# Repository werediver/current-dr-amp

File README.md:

# CURRENT DR.

This is a "current drive" or VCCS class A headphone amplifier. Some advocacy of current drive (as well as a whole book on the topic) can be found at [current-drive.info](https://www.current-drive.info/6).

The first prototype is briefly described on [Prototype](texts/prototype.md) page.

## Schematic

The current version of the schematic is showed below.

Two such channels with a dedicated [linear PSU](texts/psu.md) are going to be fit into an extruded aluminum enclosure with internal dimensions of 96x155x50 mm.

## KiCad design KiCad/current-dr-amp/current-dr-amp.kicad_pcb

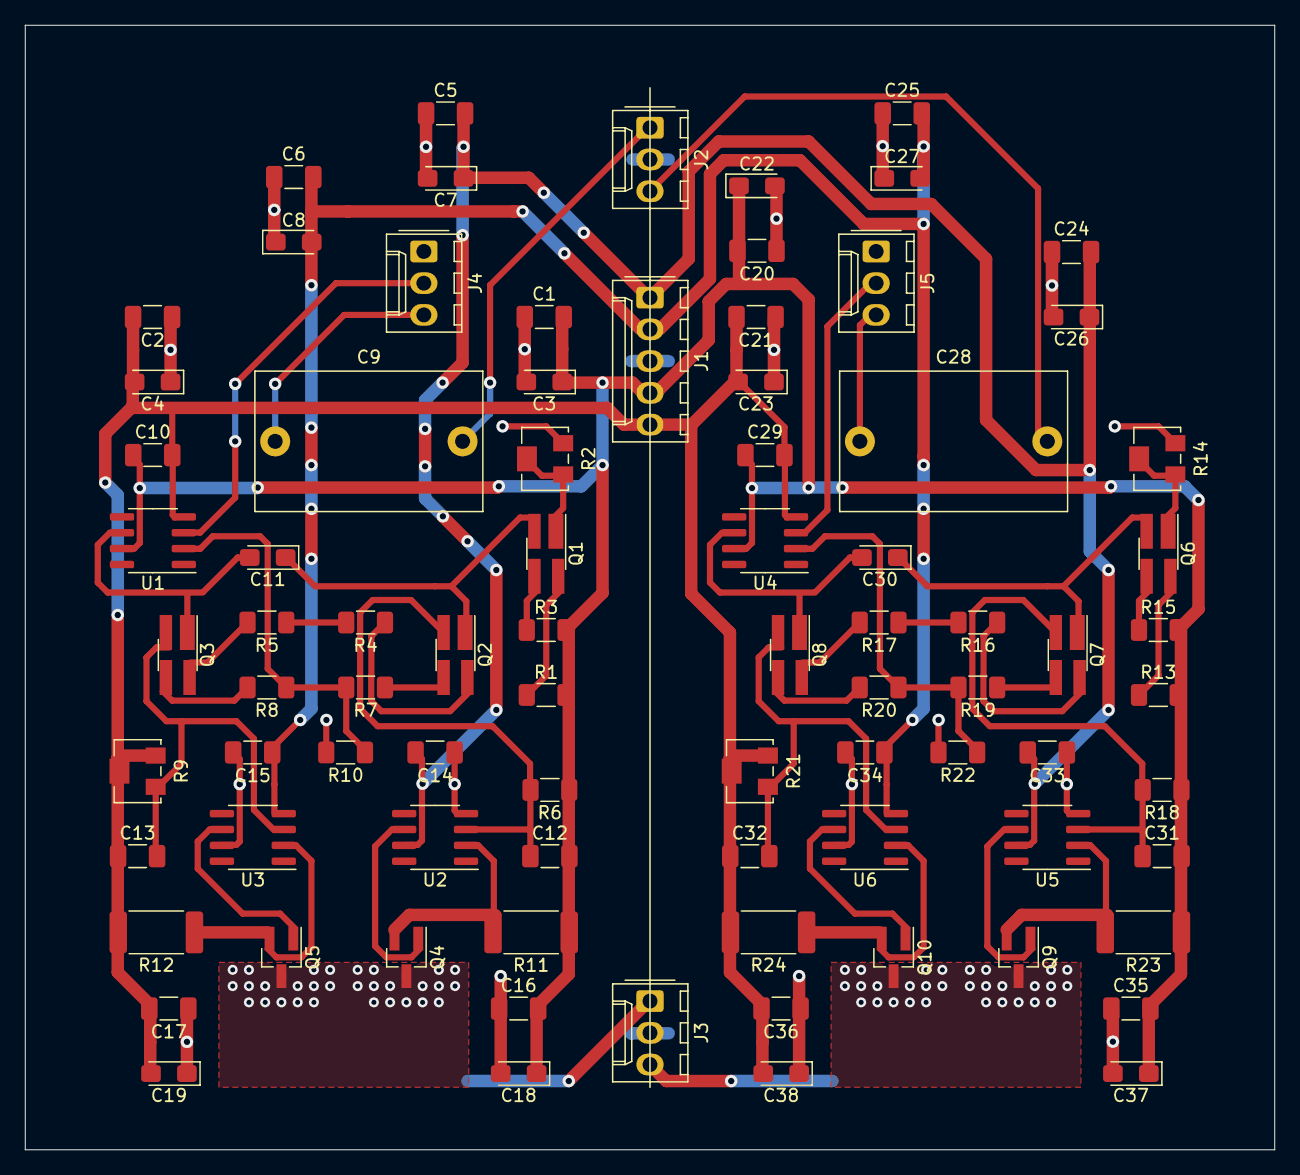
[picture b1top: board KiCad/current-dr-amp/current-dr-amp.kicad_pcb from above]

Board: 2 copper layers, 100.0 x 90.0 mm, 83 parts (0 on the bottom side), 47 nets.

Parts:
C1, C2, C5, C6, C10, C14, C15, C16, C17, C20, C21, C24, C25, C29, C33, C34, C35, C36: 0.1u; C_1206_3216Metric_Pad1.33x1.80mm_HandSolder
C3, C7, C11, C18, C19, C22, C26, C30, C37, C38: 10u; CP_EIA-3216-10_Kemet-I_Pad1.58x1.35mm_HandSolder
C4, C8, C23, C27: 22u; CP_EIA-3216-10_Kemet-I_Pad1.58x1.35mm_HandSolder
C9, C28: 2.2u; C_Rect_L18.0mm_W11.0mm_P15.00mm_FKS3_FKP3
C12, C13, C31, C32: 56p; C_1206_3216Metric_Pad1.33x1.80mm_HandSolder
J1: POWER; Molex_KK-254_AE-6410-05A_1x05_P2.54mm_Vertical
J2: IN; Molex_KK-254_AE-6410-03A_1x03_P2.54mm_Vertical
J3: OUT; Molex_KK-254_AE-6410-03A_1x03_P2.54mm_Vertical
J4, J5: ATT; Molex_KK-254_AE-6410-03A_1x03_P2.54mm_Vertical
Q1, Q3, Q6, Q8: BCM62B; SOT-143_Handsoldering
Q2, Q7: BCM61B; SOT-143_Handsoldering
Q4, Q9: BC807; SOT-23_Handsoldering
Q5, Q10: BC817; SOT-23_Handsoldering
R1, R3, R4, R5, R7, R8, R13, R15, R16, R17, R19, R20: 1k; R_1206_3216Metric_Pad1.30x1.75mm_HandSolder
R2, R14: 10k; Potentiometer_Bourns_3224W_Vertical
R6, R10, R18, R22: 680; R_1206_3216Metric_Pad1.30x1.75mm_HandSolder
R9, R21: 1k; Potentiometer_Bourns_3224W_Vertical
R11, R12, R23, R24: 15 2W; R_2512_6332Metric_Pad1.40x3.35mm_HandSolder
U1, U4: OPA1641; SOIC-8_3.9x4.9mm_P1.27mm
U2, U3, U5, U6: OPA1611; SOIC-8_3.9x4.9mm_P1.27mm

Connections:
/Channel L/IN: C9.2, J2.1
/Channel L/OUT: J3.1, Q4.3, Q5.3
/Channel R/IN: C28.2, J2.3
/Channel R/OUT: J3.3, Q9.3, Q10.3
GND: C1.1, C2.1, C3.2, C4.1, C5.1, C6.1, C7.2, C8.1, C14.1, C15.2, C16.1, C17.1, C18.2, C19.1, C20.1, C21.1, C22.2, C23.1, C24.1, C25.1, C26.2, C27.1, C33.1, C34.2, C35.1, C36.1, C37.2, C38.1, J1.3, J2.2, J3.2, J4.1, J5.1, R2.3, R10.2, R14.3, R22.2, U2.4, U3.7, U5.4, U6.7
unnamed: C9.1, J4.3
unnamed: C11.1, Q1.2, Q2.1
unnamed: C11.2, Q3.1, U1.6
unnamed: C12.1, Q2.2, R6.2, U2.3
unnamed: C13.2, Q3.2, R9.1, U3.3
unnamed: C28.1, J5.3
unnamed: C30.1, Q6.2, Q7.1
unnamed: C30.2, Q8.1, U4.6
unnamed: C31.1, Q7.2, R18.2, U5.3
unnamed: C32.2, Q8.2, R21.1, U6.3
unnamed: J4.2, U1.3
unnamed: J5.2, U4.3
unnamed: Q1.1, R2.1, R2.2
unnamed: Q1.3, R3.1
unnamed: Q1.4, R1.1
unnamed: Q2.3, R7.1
unnamed: Q2.4, R4.1
unnamed: Q3.3, R8.2
unnamed: Q3.4, R5.2
unnamed: Q4.1, U2.6
unnamed: Q4.2, R11.2, U2.2
unnamed: Q5.1, U3.6
unnamed: Q5.2, R12.1, U3.2
unnamed: Q6.1, R14.1, R14.2
unnamed: Q6.3, R15.1
unnamed: Q6.4, R13.1
unnamed: Q7.3, R19.1
unnamed: Q7.4, R16.1
unnamed: Q8.3, R20.2
unnamed: Q8.4, R17.2
unnamed: Q9.1, U5.6
unnamed: Q9.2, R23.2, U5.2
unnamed: Q10.1, U6.6
unnamed: Q10.2, R24.1, U6.2
unnamed: R4.2, R5.1
unnamed: R7.2, R8.1, R10.1, U1.2
unnamed: R16.2, R17.1
unnamed: R19.2, R20.1, R22.1, U4.2
Vcc: C1.2, C3.1, C10.1, C12.2, C16.2, C18.1, C20.2, C22.1, C29.1, C31.2, C35.2, C37.1, J1.4, R1.2, R3.2, R6.1, R11.1, R13.2, R15.2, R18.1, R23.1, U1.7, U4.7
Vcc_hi: C5.2, C7.1, C14.2, C24.2, C26.1, C33.2, J1.1, U2.7, U5.7
Vee: C2.2, C4.2, C10.2, C13.1, C17.2, C19.2, C21.2, C23.2, C29.2, C32.1, C36.2, C38.2, J1.5, R9.2, R9.3, R12.2, R21.2, R21.3, R24.2, U1.4, U4.4
Vee_hi: C6.2, C8.2, C15.1, C25.2, C27.2, C34.1, J1.2, U3.4, U6.4

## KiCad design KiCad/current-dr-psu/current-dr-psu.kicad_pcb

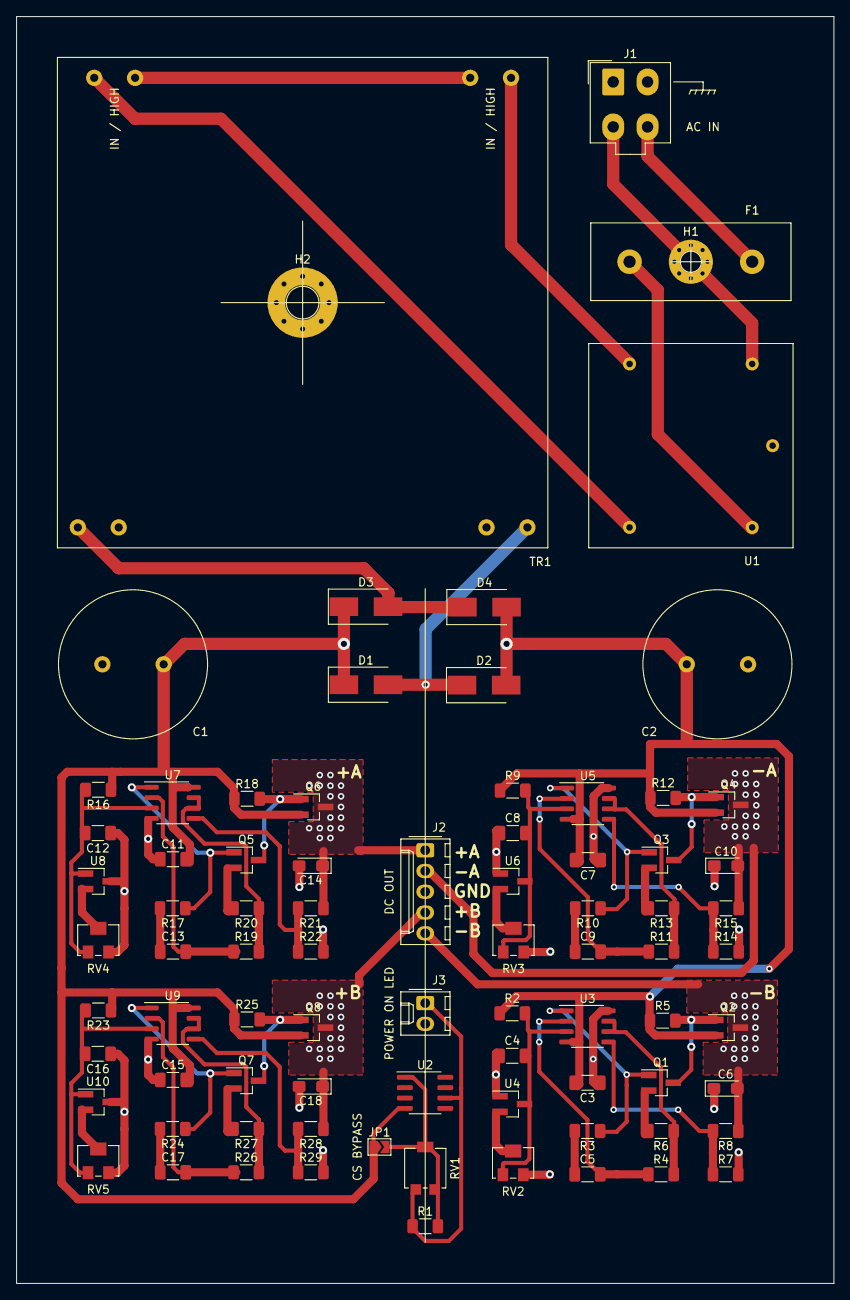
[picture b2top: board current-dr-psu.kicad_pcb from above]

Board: 2 copper layers, 100.0 x 155.0 mm, 82 parts (0 on the bottom side), 53 nets.

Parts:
C1, C2: 10000u; C_Radial_D18.0mm_H35.5mm_P7.50mm
C3, C7, C11, C15: 0.1u; C_1206_3216Metric_Pad1.33x1.80mm_HandSolder
C4, C8, C12, C16: 1n; C_1206_3216Metric_Pad1.33x1.80mm_HandSolder
C5, C9, C13, C17: 47n; C_1206_3216Metric_Pad1.33x1.80mm_HandSolder
C6, C10, C14, C18: 10u; CP_EIA-3216-10_Kemet-I_Pad1.58x1.35mm_HandSolder
D1, D2, D3, D4: STPS2L40U; D_SMB_Handsoldering
F1: 0.25A 250V; FUSE_5x20_Stelvio-Kontek_PTF75
H1: F mounting hole; MountingHole_2.7mm_Pad_Via
H2: TR mounting hole; MountingHole_4.3mm_M4_Pad_Via
J1: AC IN; Molex_Mini-Fit_Jr_5566-04A_2x02_P4.20mm_Vertical
J2: DC OUT; Molex_KK-254_AE-6410-05A_1x05_P2.54mm_Vertical
J3: POWER ON LED; Molex_KK-254_AE-6410-02A_1x02_P2.54mm_Vertical
JP1: CS BYPASS; SolderJumper-2_P1.3mm_Open_TrianglePad1.0x1.5mm
Q1, Q3: BC857A; SOT-23_Handsoldering
Q2, Q4: BC817-40; SOT-23_Handsoldering
Q5, Q7: BC847A; SOT-23_Handsoldering
Q6, Q8: BC807-40; SOT-23_Handsoldering
R1, R5, R6, R12, R13, R18, R20, R25, R27: 1k; R_1206_3216Metric_Pad1.30x1.75mm_HandSolder
R2, R3, R4, R7, R8, R9, R10, R11, R14, R15, R16, R17, R19, R21, R22, R23, R24, R26, R28, R29: 10k; R_1206_3216Metric_Pad1.30x1.75mm_HandSolder
RV1: 1k; Potentiometer_Bourns_3214G_Horizontal
RV2, RV3, RV4, RV5: 20k; Potentiometer_Bourns_3224W_Vertical
TR1: TALEMA 70063K; TF_60x60
U1: AP-01, Ohmite; EMI_FILTER_25x25
U2: LM334M; SOIC-8_3.9x4.9mm_P1.27mm
U3, U5, U7, U9: TL072; SO-8_3.9x4.9mm_P1.27mm
U4, U6, U8, U10: TS432; SOT-23_Handsoldering

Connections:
/REG NEG A/IN: C2.2, C3.2, C7.2, D2.2, D4.2, Q2.2, Q4.2, R2.1, R5.1, R9.1, R12.1, U3.4, U5.4
/REG NEG A/OUT: C10.2, J2.2, Q4.3, R15.1
/REG NEG B/OUT: C6.2, J2.5, Q2.3, R8.1
/REG POS A/IN: C1.1, C11.2, C15.2, D1.1, D3.1, JP1.1, Q6.2, Q8.2, R16.1, R18.1, R23.1, R25.1, U2.4, U7.8, U9.8
/REG POS A/OUT: C14.1, J2.1, Q6.3, R21.1
/REG POS B/OUT: C18.1, J2.4, Q8.3, R28.1
GND: C1.2, C2.1, C3.1, C4.1, C6.1, C7.1, C8.1, C10.1, C11.1, C12.1, C14.2, C15.1, C16.1, C18.2, H2.1, J1.1, J1.2, J2.3, J3.2, R7.2, R14.2, R22.2, R29.2, RV2.3, RV3.3, RV4.3, RV5.3, TR1.6, TR1.7, U1.2, U3.8, U4.1, U5.8, U6.1, U7.4, U8.3, U9.4, U10.3
unnamed: C4.2, R2.2, RV2.1, U3.3, U4.3
unnamed: C5.1, R3.2
unnamed: C5.2, R4.1, U3.2
unnamed: C8.2, R9.2, RV3.1, U5.3, U6.3
unnamed: C9.1, R10.2
unnamed: C9.2, R11.1, U5.2
unnamed: C12.2, R16.2, RV4.1, U7.3, U8.1
unnamed: C13.1, R17.2
unnamed: C13.2, R19.1, U7.2
unnamed: C16.2, R23.2, RV5.1, U9.3, U10.1
unnamed: C17.1, R24.2
unnamed: C17.2, R26.1, U9.2
unnamed: D1.2, D2.1, TR1.8
unnamed: D3.2, D4.1, TR1.5
unnamed: F1.1, J1.4
unnamed: F1.2, U1.1
unnamed: H1.1, J1.3, U1.3
unnamed: J3.1, R1.1, RV1.3, U2.6
unnamed: JP1.2, R1.2, RV1.1, RV1.2, U2.1
unnamed: Q1.1, R3.1, U3.1
unnamed: Q1.2, R6.2
unnamed: Q1.3, Q2.1, R5.2
unnamed: Q3.1, R10.1, U5.1
unnamed: Q3.2, R13.2
unnamed: Q3.3, Q4.1, R12.2
unnamed: Q5.1, R17.1, U7.1
unnamed: Q5.2, R20.2
unnamed: Q5.3, Q6.1, R18.2
unnamed: Q7.1, R24.1, U9.1
unnamed: Q7.2, R27.2
unnamed: Q7.3, Q8.1, R25.2
unnamed: R4.2, R6.1, U3.6, U3.7
unnamed: R7.1, R8.2, U3.5
unnamed: R11.2, R13.1, U5.6, U5.7
unnamed: R14.1, R15.2, U5.5
unnamed: R19.2, R20.1, U7.6, U7.7
unnamed: R21.2, R22.1, U7.5
unnamed: R26.2, R27.1, U9.6, U9.7
unnamed: R28.2, R29.1, U9.5
unnamed: RV2.2, U4.2
unnamed: RV3.2, U6.2
unnamed: RV4.2, U8.2
unnamed: RV5.2, U10.2
unnamed: TR1.1, U1.4
unnamed: TR1.2, TR1.3
unnamed: TR1.4, U1.5

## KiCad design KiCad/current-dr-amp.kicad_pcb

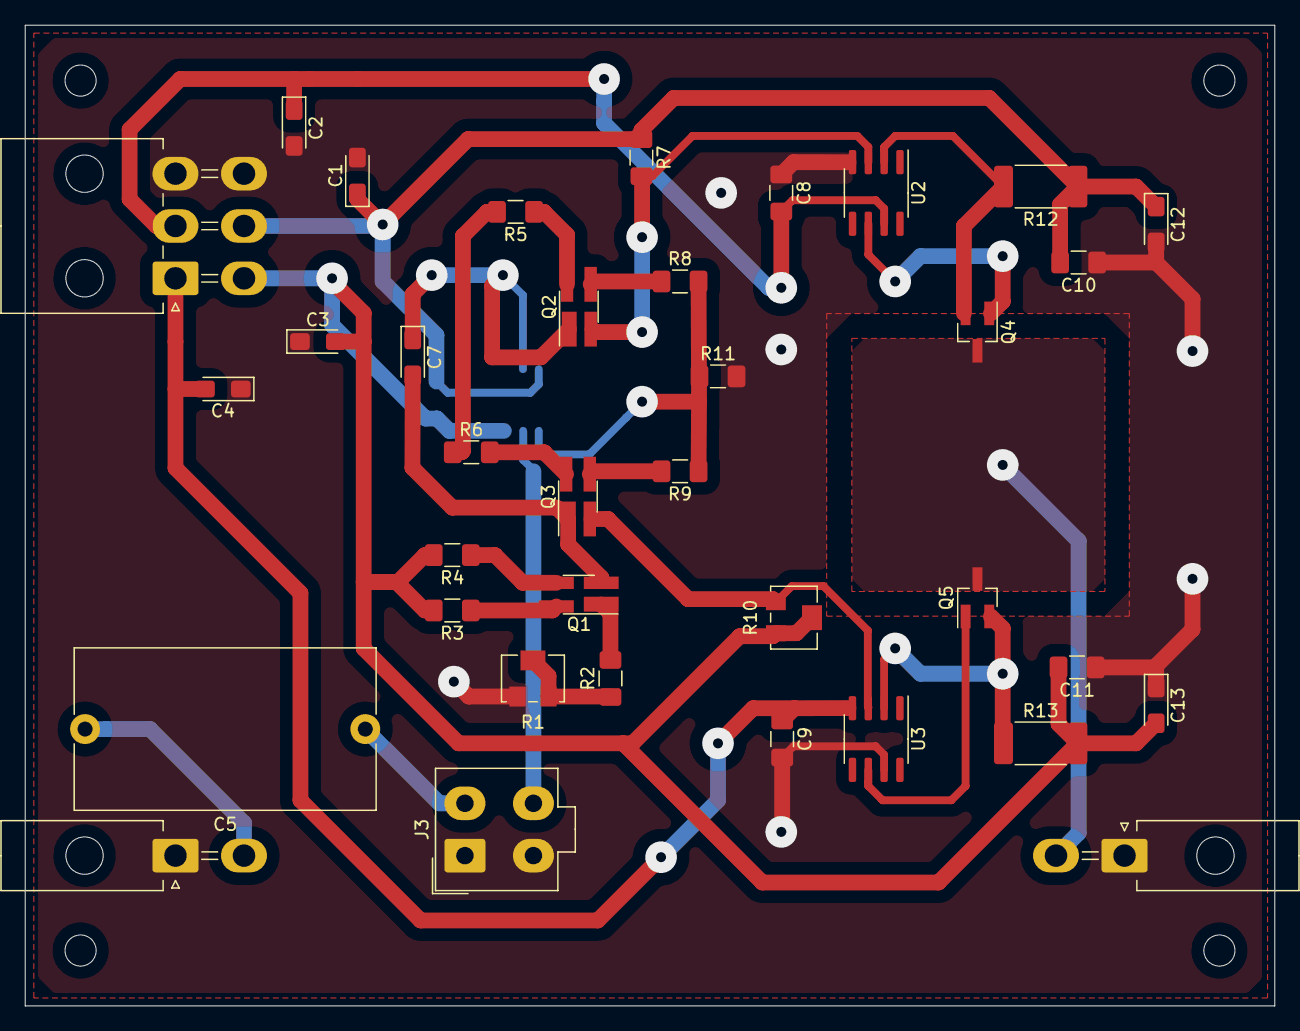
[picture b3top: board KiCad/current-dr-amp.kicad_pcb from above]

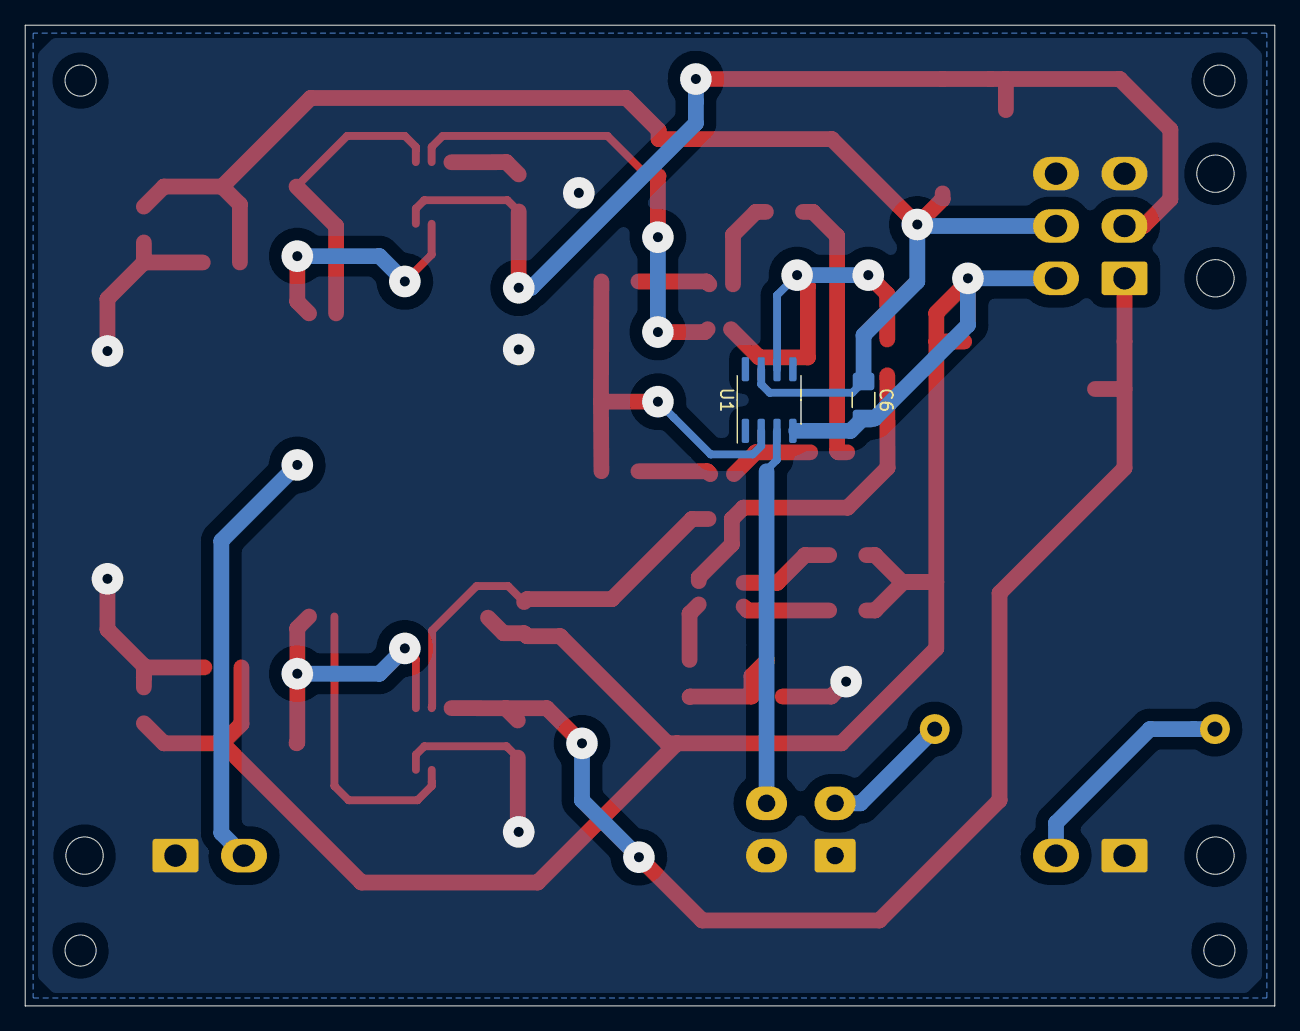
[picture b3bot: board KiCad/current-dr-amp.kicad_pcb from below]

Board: 2 copper layers, 100.3 x 78.7 mm, 38 parts (2 on the bottom side), 27 nets.

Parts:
C1, C2, C7, C12, C13: 10u; CP_EIA-3216-10_Kemet-I_Pad1.58x1.35mm_HandSolder
C3, C4: 22u; CP_EIA-3216-10_Kemet-I_Pad1.58x1.35mm_HandSolder
C5: 4u; C_Rect_L24.0mm_W12.8mm_P22.50mm_MKT
C6, C8, C9, C10, C11: 0.1u; C_1206_3216Metric_Pad1.42x1.75mm_HandSolder
J1: POWER; Molex_Mini-Fit_Jr_5569-06A2_2x03_P4.20mm_Horizontal
J2: LINE_IN; Molex_Mini-Fit_Jr_5569-02A2_2x01_P4.20mm_Horizontal
J3: ATT; Molex_Mini-Fit_Jr_5566-04A_2x02_P4.20mm_Vertical
J4: LINE_OUT; Molex_Mini-Fit_Jr_5569-02A2_2x01_P4.20mm_Horizontal
Q1, Q2: BCM61B; SOT-143_Handsoldering
Q3: BCM62B; SOT-143_Handsoldering
Q4: BC807; SOT-23_Handsoldering
Q5: BC817; SOT-23_Handsoldering
R1: 10k; Potentiometer_Bourns_3224W_Vertical
R2, R3, R4: 0; R_1206_3216Metric_Pad1.42x1.75mm_HandSolder
R5, R6, R8, R9: 400; R_1206_3216Metric_Pad1.42x1.75mm_HandSolder
R7, R11: 600; R_1206_3216Metric_Pad1.42x1.75mm_HandSolder
R10: 1k; Potentiometer_Bourns_3224W_Vertical
R12, R13: 22; R_2512_6332Metric_Pad1.52x3.35mm_HandSolder
U1: OPA1641; SOIC-8_3.9x4.9mm_P1.27mm
U2, U3: OPA1611; SOIC-8_3.9x4.9mm_P1.27mm

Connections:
GND: C1.2, C2.2, C3.1, C4.1, C8.1, C9.2, C10.1, C11.1, C12.2, C13.1, J1.3, J1.6, J2.1, J3.1, J3.3, J4.1, R1.1, R11.2, U2.4, U3.7
unnamed: C5.1, J3.2
unnamed: C5.2, J2.2
unnamed: C7.1, Q2.1, U1.6
unnamed: C7.2, Q1.2, Q3.1
unnamed: J3.4, U1.3
unnamed: J4.2, Q4.3, Q5.3
unnamed: Q1.1, R2.2
unnamed: Q1.3, R4.1
unnamed: Q1.4, R3.1
unnamed: Q2.2, R7.2, U2.3
unnamed: Q2.3, R8.1
unnamed: Q2.4, R5.1
unnamed: Q3.2, R10.1, U3.3
unnamed: Q3.3, R9.2
unnamed: Q3.4, R6.2
unnamed: Q4.1, U2.6
unnamed: Q4.2, R12.2, U2.2
unnamed: Q5.1, U3.6
unnamed: Q5.2, R13.1, U3.2
unnamed: R1.2, R1.3, R2.1
unnamed: R5.2, R6.1
unnamed: R8.2, R9.1, R11.1, U1.2
Vcc: C1.1, C6.1, C10.2, C12.1, J1.5, R7.1, R12.1, U1.7
Vcc_hi: C2.1, C8.2, J1.2, U2.7
Vee: C3.2, C6.2, C11.2, C13.2, J1.4, R3.2, R4.2, R10.2, R10.3, R13.2, U1.4
Vee_hi: C4.2, C9.1, J1.1, U3.4

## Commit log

2020-08-25 Add an LTspice model and a minimal README
2020-08-26 Add ".gitignore" to ignore some KiCad files
2020-08-26 Add a KiCad project (schematic & PCB) of a prototype version
2020-08-26 Add "Prototype" section to README
2020-08-26 Set the LTspice model to perform THD analysis by default
2020-08-26 Ignore some LTspice files
2020-08-26 Add some metadata to the schematic, update the schematic image
2020-08-29 Force Git to generate text diffs for LTspice schematics ("*.asc")
2020-08-29 Ignore more LTspice artifacts
2020-08-29 Update the LTspice model
    - use ±14/16 V instead of ±9/15V
    - increase max output current to ~236 mA (~1 W with 38 Ohm load)
    - move the quiescent current source to Vcc
2020-08-29 Update the KiCad schematic according to the LTspice model
2020-09-03 Update README
    and extract the prototype description into a separate file
2020-09-03 Fix an error in the input part of the KiCad schematic
2021-02-26 Update KiCad schematics and PCBs to the lates version
2021-02-26 Update README to present the latest schematic versions
    and to refer to the PSU description
